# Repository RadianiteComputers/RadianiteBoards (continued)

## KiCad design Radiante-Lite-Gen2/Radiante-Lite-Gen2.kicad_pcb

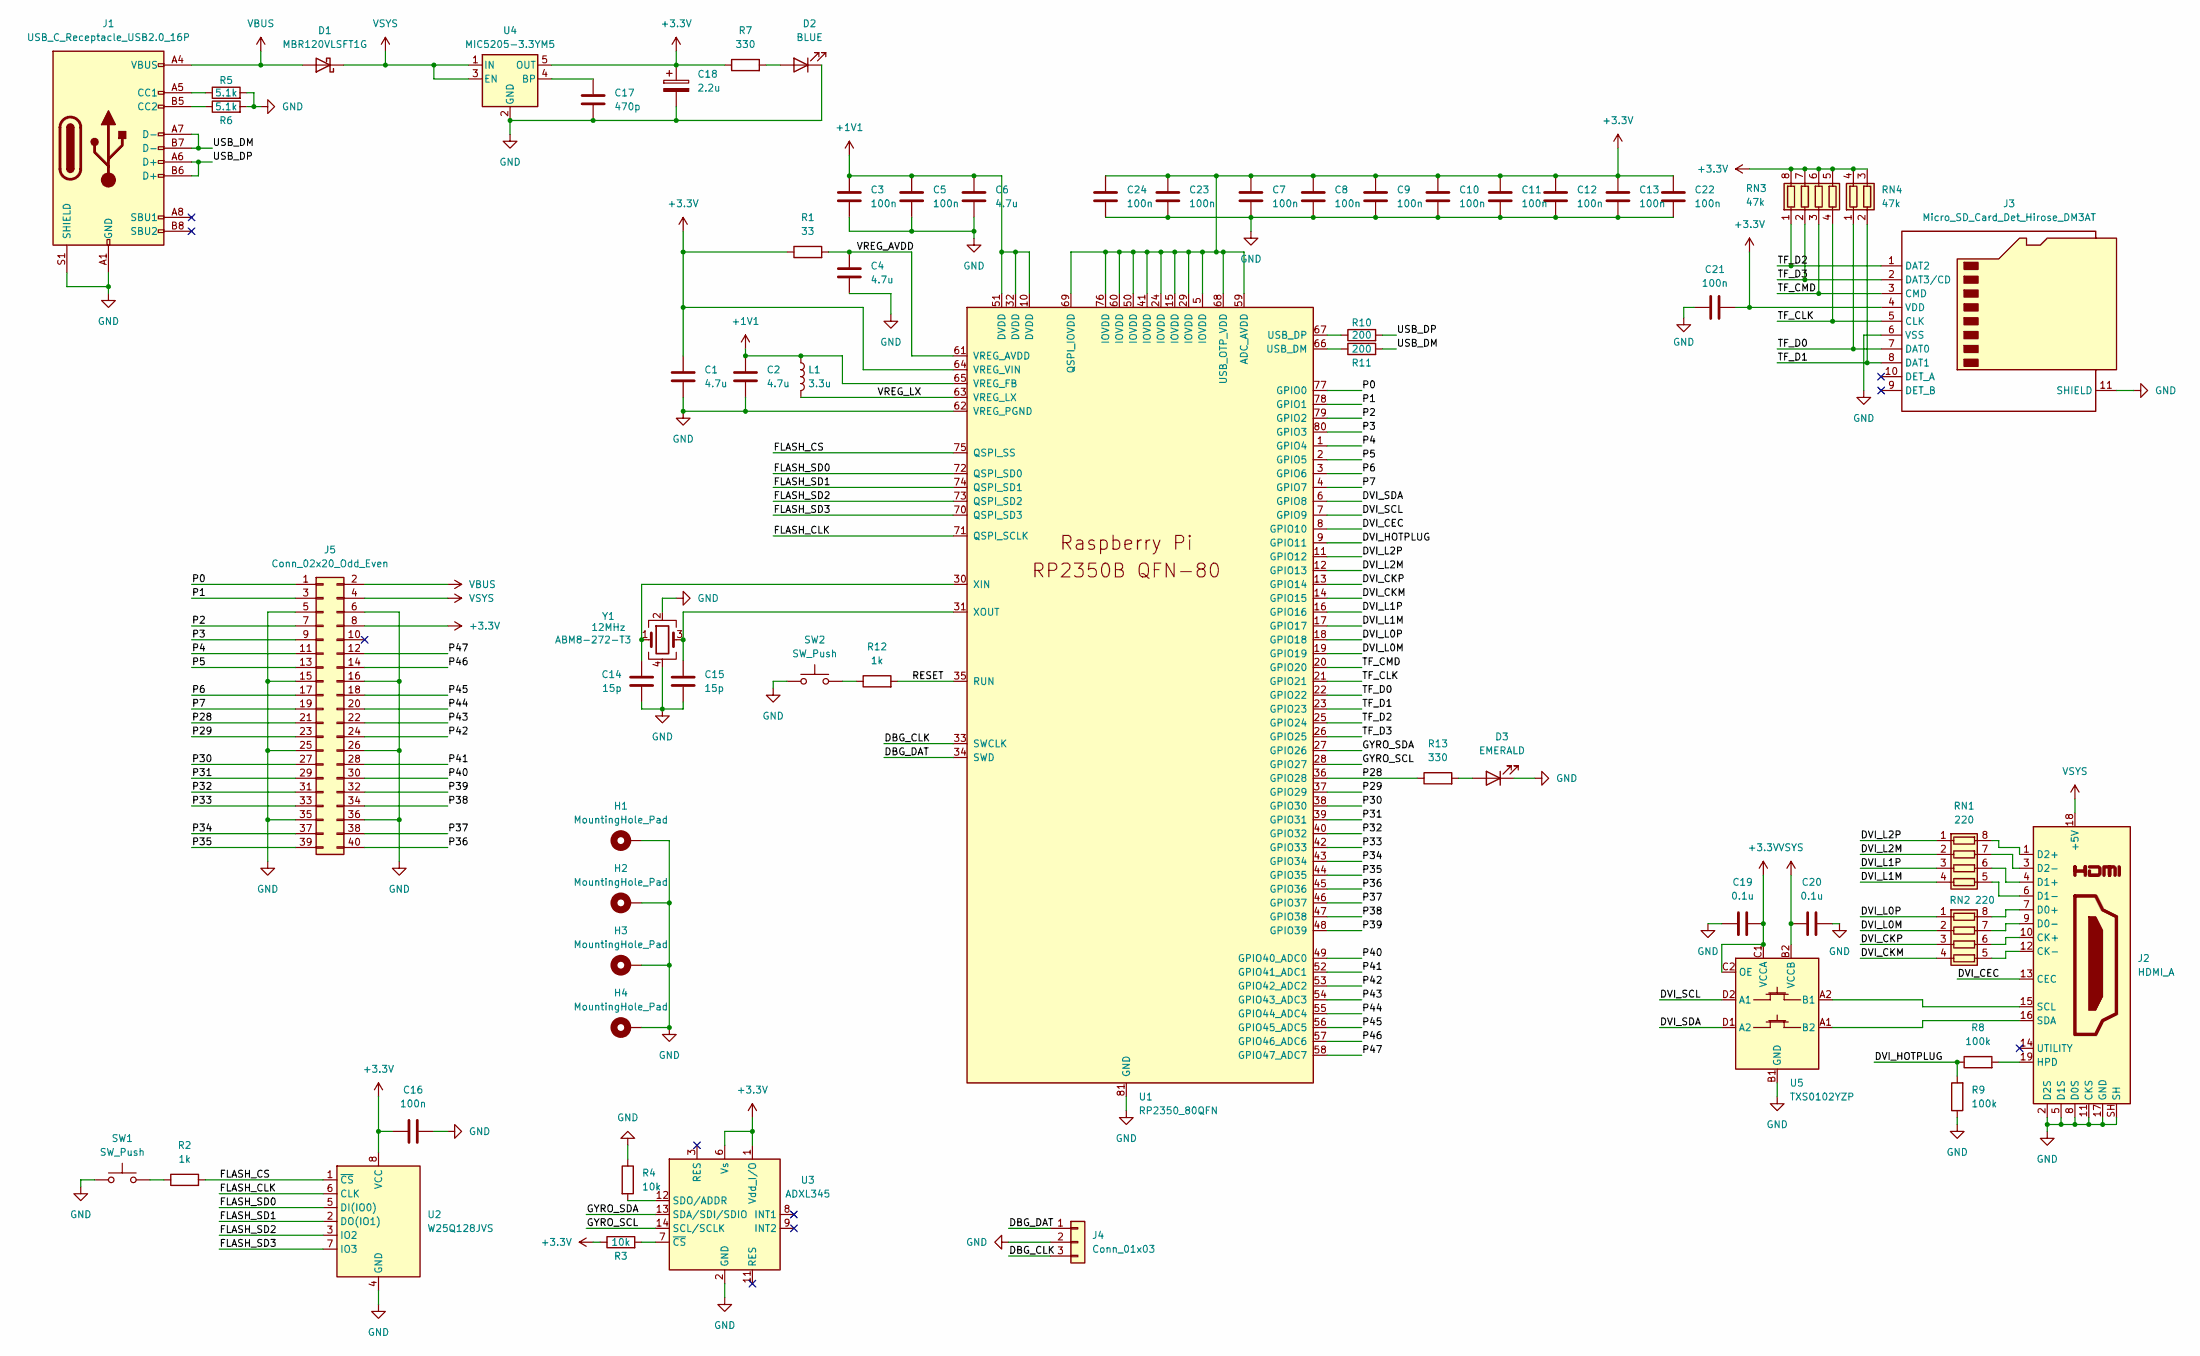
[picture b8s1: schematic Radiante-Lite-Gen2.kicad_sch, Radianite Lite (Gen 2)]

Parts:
C1, C2, C4, C6: 4.7u; C_0402_1005Metric
C3, C5, C7, C8, C9, C10, C11, C12, C13, C16, C21, C22, C23, C24: 100n; C_0402_1005Metric
C14, C15: 15p; C_0402_1005Metric
C17: 470p; C_0402_1005Metric
C18: 2.2u; CP_EIA-2012-12_Kemet-R
C19, C20: 0.1u; C_0402_1005Metric
D1: MBR120VLSFT1G; D_SOD-123F
D2: BLUE; LED_0402_1005Metric
D3: EMERALD; LED_0402_1005Metric
H1, H2, H3, H4: MountingHole_Pad; MountingHole_2.2mm_M2_Pad_TopBottom
J1: USB_C_Receptacle_USB2.0_16P; USB_C_Receptacle_GCT_USB4105-xx-A_16P_TopMnt_Horizontal
J2: HDMI_A; HDMI_A_Molex_208658-1001_Horizontal
J3: Micro_SD_Card_Det_Hirose_DM3AT; microSD_HC_Molex_104031-0811
J4: Conn_01x03; JST_SH_BM03B-SRSS-TB_1x03-1MP_P1.00mm_Vertical
J5: Conn_02x20_Odd_Even; PinHeader_2x20_P2.54mm_Vertical
L1: 3.3u; L_pol_2016
R1: 33; R_0402_1005Metric
R2, R12: 1k; R_0402_1005Metric
R3, R4: 10k; R_0402_1005Metric
R5, R6: 5.1k; R_0402_1005Metric
R7, R13: 330; R_0402_1005Metric
R8, R9: 100k; R_0402_1005Metric
R10, R11: 200; R_0402_1005Metric
RN1, RN2: 220; R_Array_Concave_4x0402
RN3: 47k; R_Array_Concave_4x0402
RN4: 47k; R_Array_Convex_2x0402
SW1, SW2: SW_Push; SW_Push_1P1T_NO_Vertical_Wuerth_434133025816
U1: RP2350_80QFN; RP2350-QFN-80-1EP_10x10_P0.4mm_EP3.4x3.4mm_ThermalVias
U2: W25Q128JVS; SOIC-8_5.23x5.23mm_P1.27mm
U3: ADXL345; LGA-14_3x5mm_P0.8mm_LayoutBorder1x6y
U4: MIC5205-3.3YM5; SOT-23-5
U5: TXS0102YZP; Texas_DSBGA-8_0.9x1.9mm_Layout2x4_P0.5mm
Y1: 12MHz; Crystal_SMD_3225-4Pin_3.2x2.5mm

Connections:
+1V1: C2.1, C3.1, C5.1, C6.1, L1.1, U1.10 (DVDD), U1.32 (DVDD), U1.51 (DVDD), U1.65 (VREG_FB)
+3.3V: C1.1, C7.1, C8.1, C9.1, C10.1, C11.1, C12.1, C13.1, C16.1, C18.1, C19.2, C21.2, C22.1, C23.1, C24.1, J3.4 (VDD), J5.8, R1.1, R3.1, R7.1, RN3.5 (R4.2), RN3.6 (R3.2), RN3.7 (R2.2), RN3.8 (R1.2), RN4.3 (R2.2), RN4.4 (R1.2), U1.5 (IOVDD), U1.15 (IOVDD), U1.24 (IOVDD), U1.29 (IOVDD), U1.41 (IOVDD), U1.50 (IOVDD), U1.59 (ADC_AVDD), U1.60 (IOVDD), U1.64 (VREG_VIN), U1.68 (USB_OTP_VDD), U1.69 (QSPI_IOVDD), U1.76 (IOVDD), U2.8 (VCC), U3.1 (Vdd_I/O), U3.6 (Vs), U4.5 (OUT), U5.C1 (VCCA), U5.C2 (OE)
/DBG_CLK: J4.3, U1.33 (SWCLK)
/DBG_DAT: J4.1, U1.34 (SWD)
/DVI_CEC: J2.13 (CEC), U1.8 (GPIO10)
/DVI_CKM: RN2.4 (R4.1), U1.14 (GPIO15)
/DVI_CKP: RN2.3 (R3.1), U1.13 (GPIO14)
/DVI_HOTPLUG: R8.1, R9.2, U1.9 (GPIO11)
/DVI_L0M: RN2.2 (R2.1), U1.19 (GPIO19)
/DVI_L0P: RN2.1 (R1.1), U1.18 (GPIO18)
/DVI_L1M: RN1.4 (R4.1), U1.17 (GPIO17)
/DVI_L1P: RN1.3 (R3.1), U1.16 (GPIO16)
/DVI_L2M: RN1.2 (R2.1), U1.12 (GPIO13)
/DVI_L2P: RN1.1 (R1.1), U1.11 (GPIO12)
/DVI_SCL: U1.7 (GPIO9), U5.D2 (A1)
/DVI_SDA: U1.6 (GPIO8), U5.D1 (A2)
/FLASH_CLK: U1.71 (QSPI_SCLK), U2.6 (CLK)
/FLASH_CS: R2.2, U1.75 (QSPI_SS), U2.1 (~CS)
/FLASH_SD0: U1.72 (QSPI_SD0), U2.5 (DI(IO0))
/FLASH_SD1: U1.74 (QSPI_SD1), U2.2 (DO(IO1))
/FLASH_SD2: U1.73 (QSPI_SD2), U2.3 (IO2)
/FLASH_SD3: U1.70 (QSPI_SD3), U2.7 (IO3)
/GYRO_SCL: U1.28 (GPIO27), U3.14 (SCL/SCLK)
/GYRO_SDA: U1.27 (GPIO26), U3.13 (SDA/SDI/SDIO)
/P0: J5.1, U1.77 (GPIO0)
/P1: J5.3, U1.78 (GPIO1)
/P2: J5.7, U1.79 (GPIO2)
/P3: J5.9, U1.80 (GPIO3)
/P4: J5.11, U1.1 (GPIO4)
/P5: J5.13, U1.2 (GPIO5)
/P6: J5.17, U1.3 (GPIO6)
/P7: J5.19, U1.4 (GPIO7)
/P28: J5.21, R13.1, U1.36 (GPIO28)
/P29: J5.23, U1.37 (GPIO29)
/P30: J5.27, U1.38 (GPIO30)
/P31: J5.29, U1.39 (GPIO31)
/P32: J5.31, U1.40 (GPIO32)
/P33: J5.33, U1.42 (GPIO33)
/P34: J5.37, U1.43 (GPIO34)
/P35: J5.39, U1.44 (GPIO35)
/P36: J5.40, U1.45 (GPIO36)
/P37: J5.38, U1.46 (GPIO37)
/P38: J5.34, U1.47 (GPIO38)
/P39: J5.32, U1.48 (GPIO39)
/P40: J5.30, U1.49 (GPIO40_ADC0)
/P41: J5.28, U1.52 (GPIO41_ADC1)
/P42: J5.24, U1.53 (GPIO42_ADC2)
/P43: J5.22, U1.54 (GPIO43_ADC3)
/P44: J5.20, U1.55 (GPIO44_ADC4)
/P45: J5.18, U1.56 (GPIO45_ADC5)
/P46: J5.14, U1.57 (GPIO46_ADC6)
/P47: J5.12, U1.58 (GPIO47_ADC7)
/RESET: R12.2, U1.35 (RUN)
/TF_CLK: J3.5 (CLK), RN3.4 (R4.1), U1.21 (GPIO21)
/TF_CMD: J3.3 (CMD), RN3.3 (R3.1), U1.20 (GPIO20)
/TF_D0: J3.7 (DAT0), RN4.1 (R1.1), U1.22 (GPIO22)
/TF_D1: J3.8 (DAT1), RN4.2 (R2.1), U1.23 (GPIO23)
/TF_D2: J3.1 (DAT2), RN3.1 (R1.1), U1.25 (GPIO24)
/TF_D3: J3.2 (DAT3/CD), RN3.2 (R2.1), U1.26 (GPIO25)
/USB_DM: J1.A7 (D-), J1.B7 (D-), R11.2
/USB_DP: J1.A6 (D+), J1.B6 (D+), R10.2
/VREG_AVDD: C4.1, R1.2, U1.61 (VREG_AVDD)
/VREG_LX: L1.2, U1.63 (VREG_LX)
GND: C1.2, C2.2, C3.2, C4.2, C5.2, C6.2, C7.2, C8.2, C9.2, C10.2, C11.2, C12.2, C13.2, C14.2, C15.2, C16.2, C17.2, C18.2, C19.1, C20.2, C21.1, C22.2, C23.2, C24.2, D2.1 (K), D3.1 (K), H1.1, H2.1, H3.1, H4.1, J1.A1 (GND), J1.A12 (GND), J1.B1 (GND), J1.B12 (GND), J1.S1 (SHIELD), J2.2 (D2S), J2.5 (D1S), J2.8 (D0S), J2.11 (CKS), J2.17 (GND), J2.SH, J3.6 (VSS), J3.11 (SHIELD), J4.2, J5.5, J5.6, J5.15, J5.16, J5.25, J5.26, J5.35, J5.36, R4.1, R5.2, R6.2, R9.1, SW1.1, SW2.1, U1.62 (VREG_PGND), U1.81 (GND), U2.4 (GND), U3.2 (GND), U3.4 (GND), U3.5 (GND), U4.2 (GND), U5.B1 (GND), Y1.2, Y1.4
unnamed: D2.2 (A), R7.2
unnamed: D3.2 (A), R13.2
unnamed: J1.A5 (CC1), R5.1
unnamed: J1.B5 (CC2), R6.1
unnamed: J2.10 (CK+), RN2.6 (R3.2)
unnamed: J2.12 (CK-), RN2.5 (R4.2)
unnamed: J2.7 (D0+), RN2.8 (R1.2)
unnamed: J2.9 (D0-), RN2.7 (R2.2)
unnamed: J2.4 (D1+), RN1.6 (R3.2)
unnamed: J2.6 (D1-), RN1.5 (R4.2)
unnamed: J2.1 (D2+), RN1.8 (R1.2)
unnamed: J2.3 (D2-), RN1.7 (R2.2)
unnamed: J2.19 (HPD), R8.2
unnamed: J2.15 (SCL), U5.A2 (B1)
unnamed: J2.16 (SDA), U5.A1 (B2)
unnamed: R2.1, SW1.2
unnamed: R12.1, SW2.2
unnamed: R11.1, U1.66 (USB_DM)
unnamed: R10.1, U1.67 (USB_DP)
unnamed: C14.1, U1.30 (XIN), Y1.1
unnamed: C15.1, U1.31 (XOUT), Y1.3
unnamed: R4.2, U3.12 (SDO/ADDR)
unnamed: R3.2, U3.7 (~CS)
unnamed: C17.1, U4.4 (BP)
VBUS: D1.2 (A), J1.A4 (VBUS), J1.A9 (VBUS), J1.B4 (VBUS), J1.B9 (VBUS), J5.2
VSYS: C20.1, D1.1 (K), J2.18 (+5V), J5.4, U4.1 (IN), U4.3 (EN), U5.B2 (VCCB)

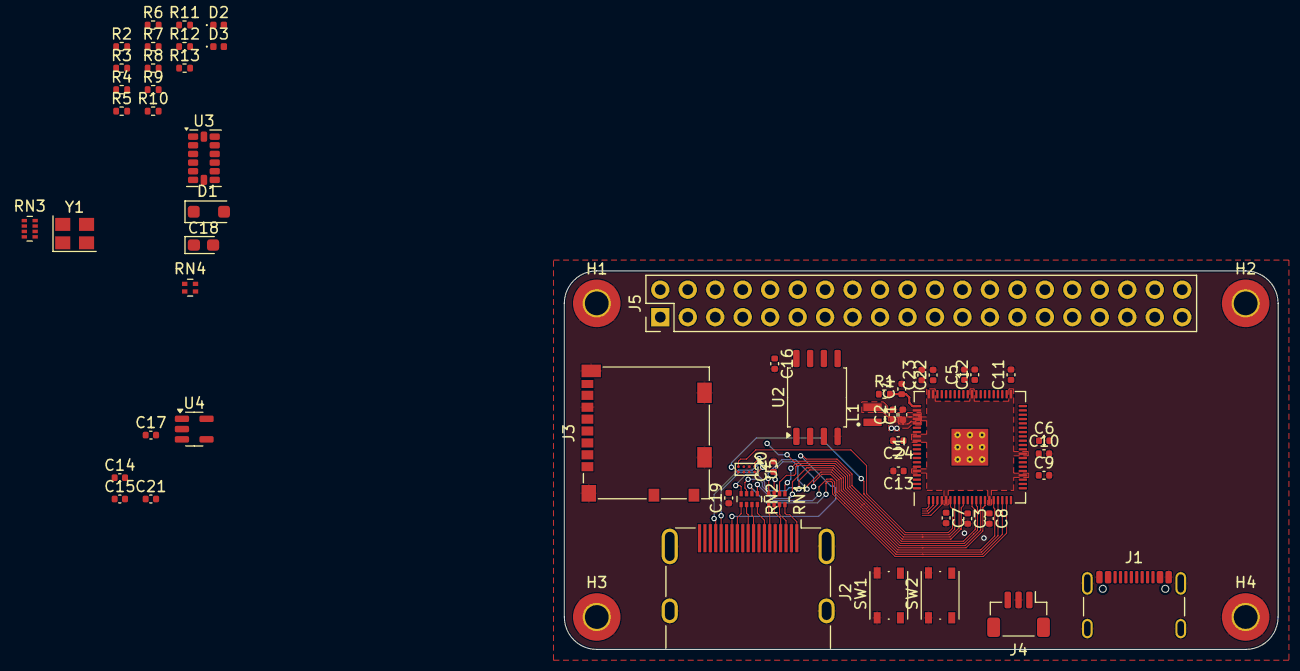
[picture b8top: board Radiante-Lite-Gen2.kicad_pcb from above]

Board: 2 copper layers, 66.0 x 35.0 mm, 62 parts (0 on the bottom side), 90 nets.

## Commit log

2024-08-26 Initial upload
2024-08-28 fix some stuff ig
2024-09-21 a lot of commit shit lol (PROJECT LEMON IRVINE FUCKED UP)
2024-09-26 fix some pcb (major rev, see on https://www.reddit.com/r/PrintedCircuitBoard/comments/1fpfia7/review_request_arduino_uno_r4_wifi_clone_using/)
2024-09-27 fix some stuff violating clearances and adding current limiting resistor
2024-10-11 fixed some data lines not abiding by the clearance (make it close)
2024-10-12 my bad for using nightly kicad
2024-10-18 revisi
2024-10-18 reverted
2024-10-20 add lite gen 2
2024-10-20 add the pcb
2024-10-20 partially laying out
2024-10-21 trying to not being a lazy fucktard on designing the lite gen 2
2024-10-22 add new product
2024-10-27 just adding more projects here lol
2024-11-22 upstream sync
2024-11-22 add new minor rev
2024-11-30 add microneo 2
2024-11-30 add stitching vias
2024-12-01 fixing drc errors
2024-12-01 fix unreasoned wiggling traces that does not affect overall impedance and integrity
2024-12-01 fix vbus copper pour to be more matched
2024-12-01 fixes to the microneo 2
2024-12-02 listening to the community, lots of changes here
2024-12-03 fix more stuffs
2024-12-03 turns out SVREF is a divided voltage between DRAM
2024-12-08 changes to some files
2024-12-08 fix copper fill and some minor stuffs
2024-12-11 woopsies, wrong sd card direction
2024-12-11 add 3d models
2024-12-13 add avaota
2024-12-17 project irvine continued
2024-12-18 additions to project irvine
2024-12-18 few changes
2025-01-04 backup
2025-03-06 6/3/2025 upstream sync
2025-04-06 add wip Project Eous
2025-06-08 added the buddy
